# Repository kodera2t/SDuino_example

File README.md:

# SDuino_example
Once I was excited to see Intel's announce that they will release "SD card sized (SD card shaped) computer", 
but it was not true. This time I made a real SD card sized full programmable (indeed, Arduino pro compatible) 
small computer board, which is released at
https://hackaday.io/project/6435-sd-card-sized-board-lets-say-sduino
On this repository, I would upload practical application of SDuino. First one is "weather forecast SDuino" wich I2C pressure sensor
Have fun!

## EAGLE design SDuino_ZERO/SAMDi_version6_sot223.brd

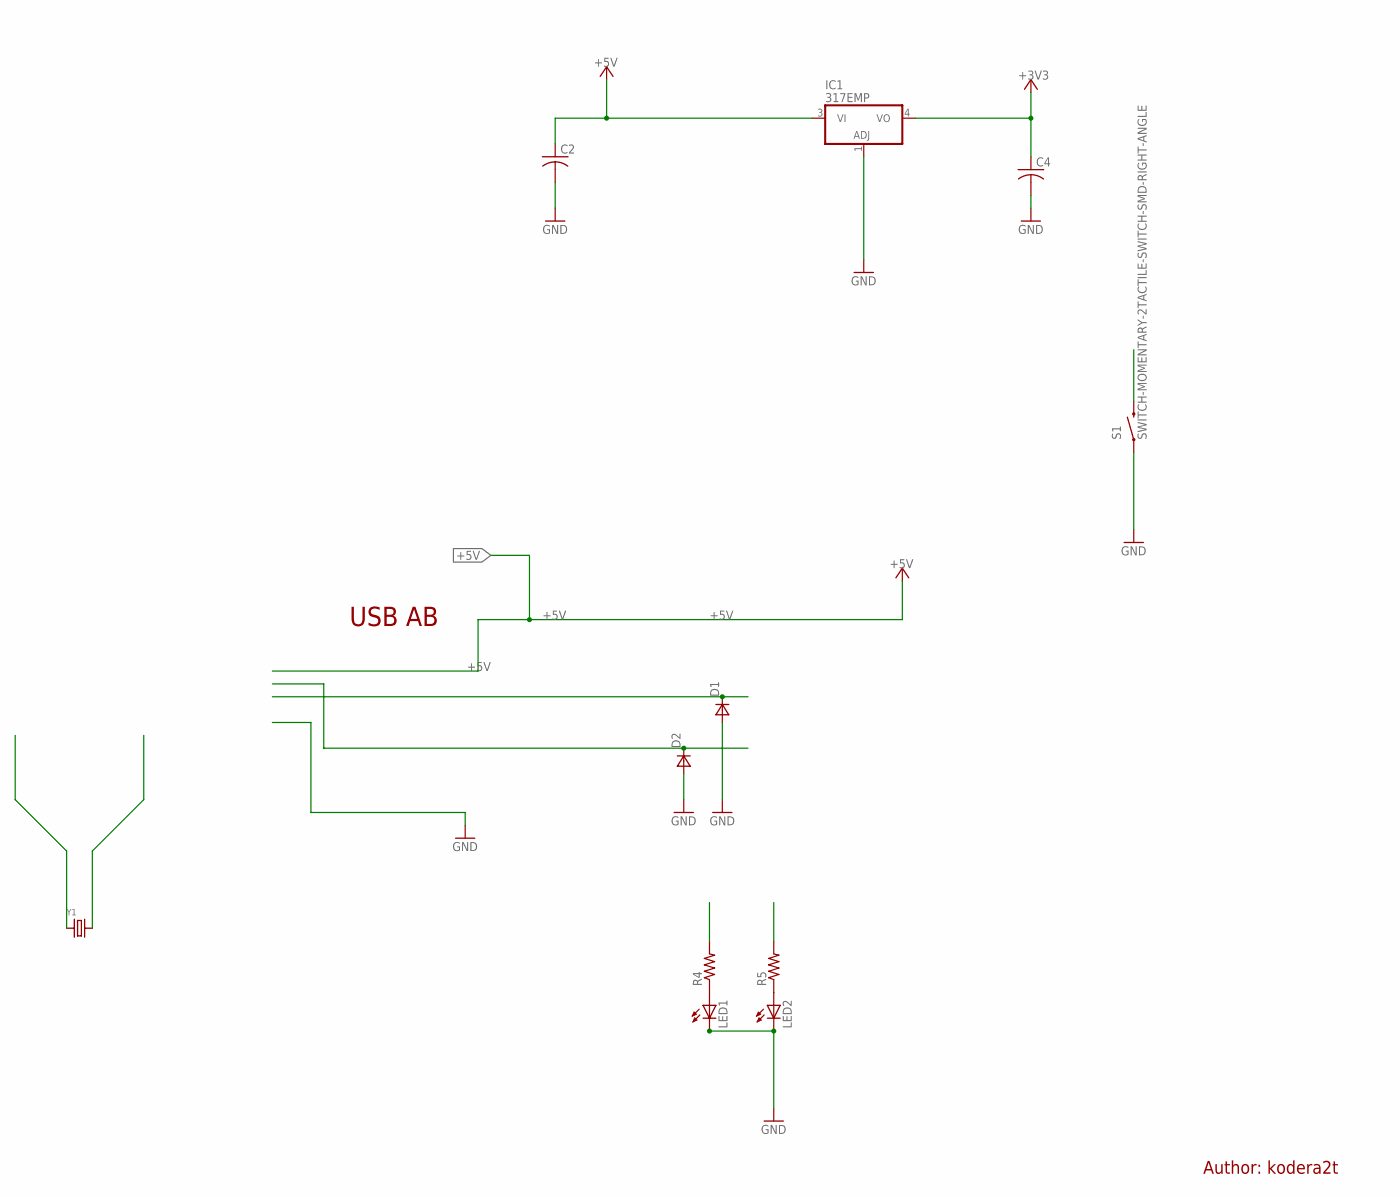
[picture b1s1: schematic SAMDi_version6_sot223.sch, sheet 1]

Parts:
C2, C4: C-USC0603; C0603
D1, D2: DSOD323; SOD323
IC1: 317EMP; SOT223
LED1, LED2: LEDCHIP-LED0603; CHIP-LED0603
R4, R5: R-US_R0603; R0603
S1: SWITCH-MOMENTARY-2TACTILE-SWITCH-SMD-RIGHT-ANGLE; TACTILE_SWITCH-SMD-RIGHT-ANGLE
Y1: CRYSTALTHIN32K; CRYSTAL_4.9X1.8

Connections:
+3V3: C4.1, IC1.4 (VO); also elsewhere on the board
+5V: C2.1, IC1.3 (VI)
GND: C2.2, C4.2, D1.2 (A), D2.2 (A), IC1.1 (ADJ), LED1.C, LED2.C, S1.1; also elsewhere on the board
LED1: R4.2; also elsewhere on the board
LED2: R5.2; also elsewhere on the board
unnamed: LED1.A, R4.1
unnamed: LED2.A, R5.1
TARGET_RESET: S1.2; also elsewhere on the board
TARGET_USB_N: D2.1 (C); also elsewhere on the board
TARGET_USB_P: D1.1 (C); also elsewhere on the board
XTAL11: Y1.2; also elsewhere on the board
XTAL22: Y1.1; also elsewhere on the board

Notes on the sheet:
USB AB
Author: kodera2t

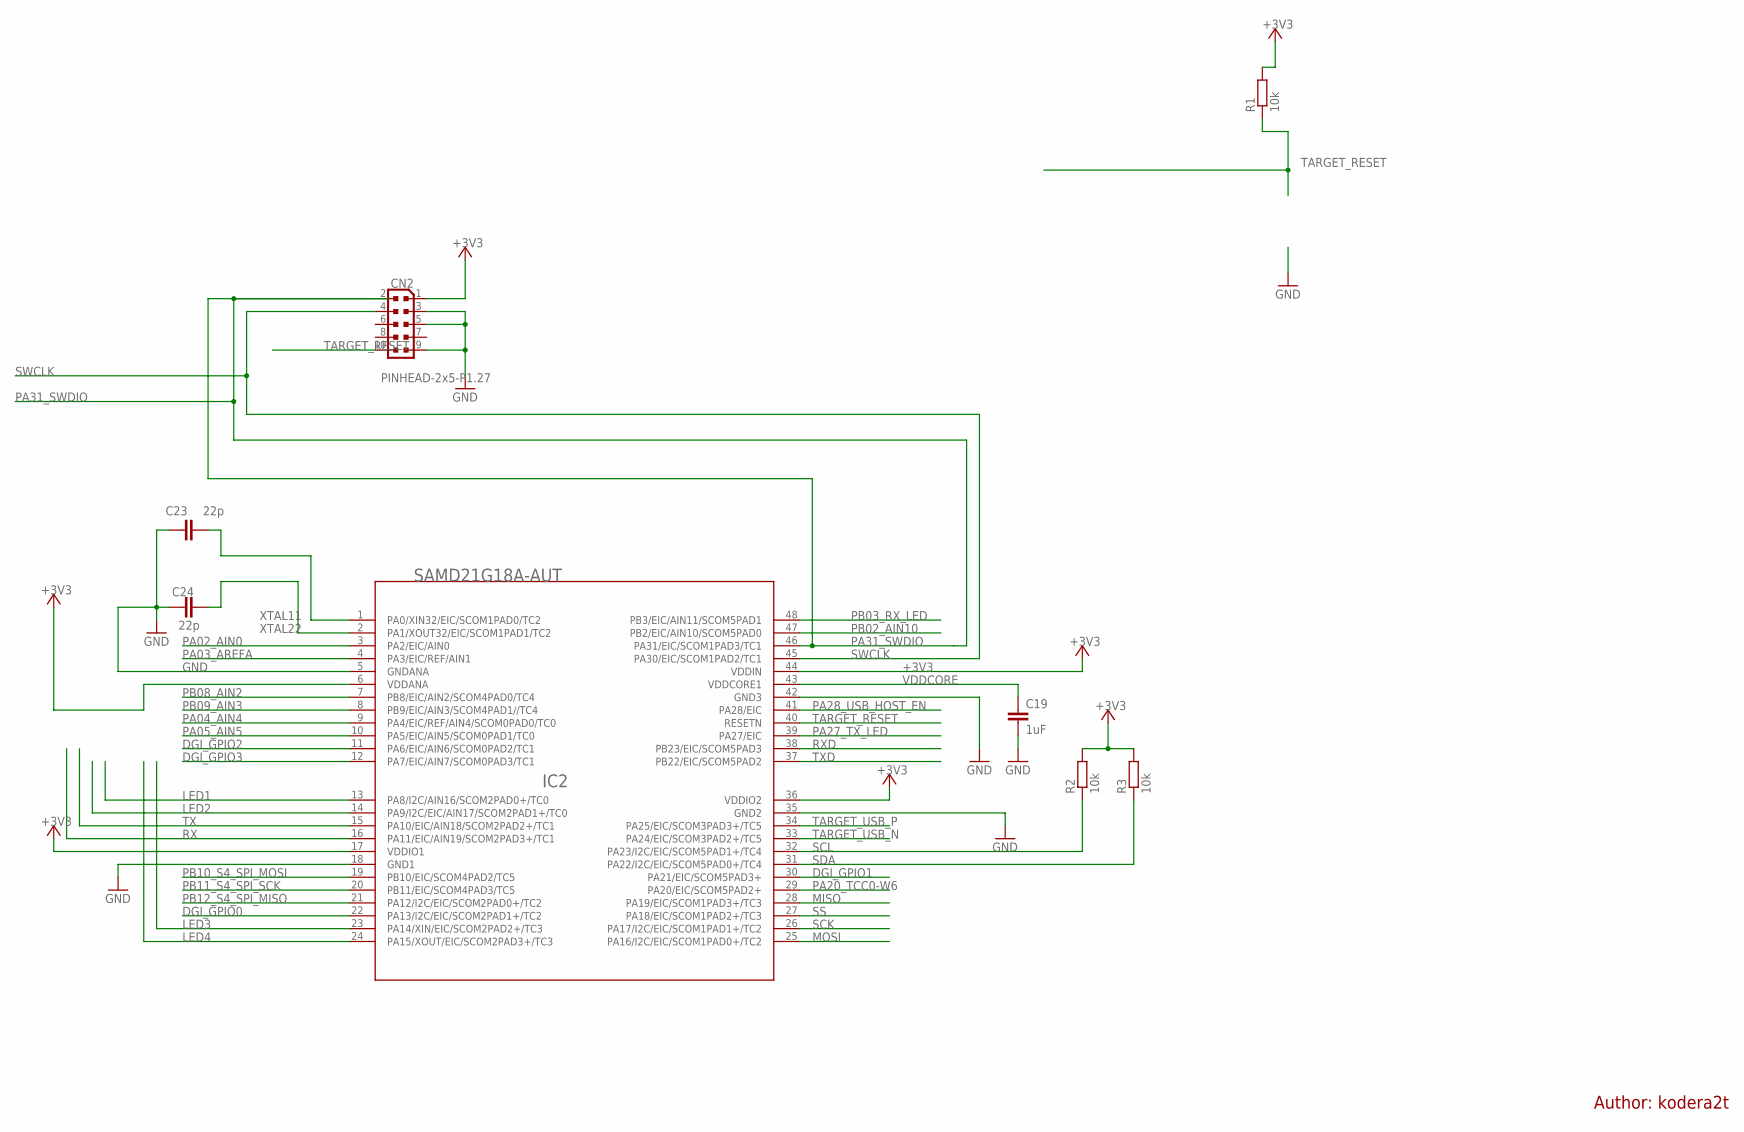
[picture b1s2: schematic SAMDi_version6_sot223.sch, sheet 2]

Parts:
C19: 1uF; C0603-ROUND
C23, C24: 22p; C0603-ROUND
CN2: PINHEAD-2x5-P1.27; PINHEAD_2X05_127
IC2: SAMD21G18A-AUT; TQFP48-7X7
R1, R2, R3: 10k; R0603-ROUND

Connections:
+3V3: CN2.1, IC2.6 (VDDANA), IC2.17 (VDDIO1), IC2.36 (VDDIO2), IC2.44 (VDDIN), R1.2, R2.2, R3.2; also elsewhere on the board
DGI_GPIO0: IC2.22 (PA13/I2C/EIC/SCOM2PAD1+/TC2)
DGI_GPIO1: IC2.30 (PA21/EIC/SCOM5PAD3+)
DGI_GPIO2: IC2.11 (PA6/EIC/AIN6/SCOM0PAD2/TC1)
DGI_GPIO3: IC2.12 (PA7/EIC/AIN7/SCOM0PAD3/TC1)
GND: C19.2, C23.1, C24.1, CN2.3, CN2.5, CN2.9, IC2.5 (GNDANA), IC2.18 (GND1), IC2.35 (GND2), IC2.42 (GND3); also elsewhere on the board
LED1: IC2.13 (PA8/I2C/AIN16/SCOM2PAD0+/TC0); also elsewhere on the board
LED2: IC2.14 (PA9/I2C/EIC/AIN17/SCOM2PAD1+/TC0); also elsewhere on the board
LED3: IC2.23 (PA14/XIN/EIC/SCOM2PAD2+/TC3)
LED4: IC2.24 (PA15/XOUT/EIC/SCOM2PAD3+/TC3)
MISO: IC2.28 (PA19/EIC/SCOM1PAD3+/TC3)
MOSI: IC2.25 (PA16/I2C/EIC/SCOM1PAD0+/TC2)
PA02_AIN0: IC2.3 (PA2/EIC/AIN0)
PA03_AREFA: IC2.4 (PA3/EIC/REF/AIN1)
PA04_AIN4: IC2.9 (PA4/EIC/REF/AIN4/SCOM0PAD0/TC0)
PA05_AIN5: IC2.10 (PA5/EIC/AIN5/SCOM0PAD1/TC0)
PA20_TCC0-W6: IC2.29 (PA20/EIC/SCOM5PAD2+)
PA27_TX_LED: IC2.39 (PA27/EIC)
PA28_USB_HOST_EN: IC2.41 (PA28/EIC)
PA31_SWDIO: CN2.2, IC2.46 (PA31/EIC/SCOM1PAD3/TC1)
PB02_AIN10: IC2.47 (PB2/EIC/AIN10/SCOM5PAD0)
PB03_RX_LED: IC2.48 (PB3/EIC/AIN11/SCOM5PAD1)
PB08_AIN2: IC2.7 (PB8/EIC/AIN2/SCOM4PAD0/TC4)
PB09_AIN3: IC2.8 (PB9/EIC/AIN3/SCOM4PAD1//TC4)
PB10_S4_SPI_MOSI: IC2.19 (PB10/EIC/SCOM4PAD2/TC5)
PB11_S4_SPI_SCK: IC2.20 (PB11/EIC/SCOM4PAD3/TC5)
PB12_S4_SPI_MISO: IC2.21 (PA12/I2C/EIC/SCOM2PAD0+/TC2)
RX: IC2.16 (PA11/EIC/AIN19/SCOM2PAD3+/TC1)
RXD: IC2.38 (PB23/EIC/SCOM5PAD3)
SCK: IC2.26 (PA17/I2C/EIC/SCOM1PAD1+/TC2)
SCL: IC2.32 (PA23/I2C/EIC/SCOM5PAD1+/TC4), R2.1
SDA: IC2.31 (PA22/I2C/EIC/SCOM5PAD0+/TC4), R3.1
SS: IC2.27 (PA18/EIC/SCOM1PAD2+/TC3)
SWCLK: CN2.4, IC2.45 (PA30/EIC/SCOM1PAD2/TC1)
TARGET_RESET: CN2.10, IC2.40 (RESETN), R1.1; also elsewhere on the board
TARGET_USB_N: IC2.33 (PA24/EIC/SCOM3PAD2+/TC5); also elsewhere on the board
TARGET_USB_P: IC2.34 (PA25/EIC/SCOM3PAD3+/TC5); also elsewhere on the board
TX: IC2.15 (PA10/EIC/AIN18/SCOM2PAD2+/TC1)
TXD: IC2.37 (PB22/EIC/SCOM5PAD2)
VDDCORE: C19.1, IC2.43 (VDDCORE1)
XTAL11: C23.2, IC2.1 (PA0/XIN32/EIC/SCOM1PAD0/TC2); also elsewhere on the board
XTAL22: C24.2, IC2.2 (PA1/XOUT32/EIC/SCOM1PAD1/TC2); also elsewhere on the board

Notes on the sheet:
Author: kodera2t

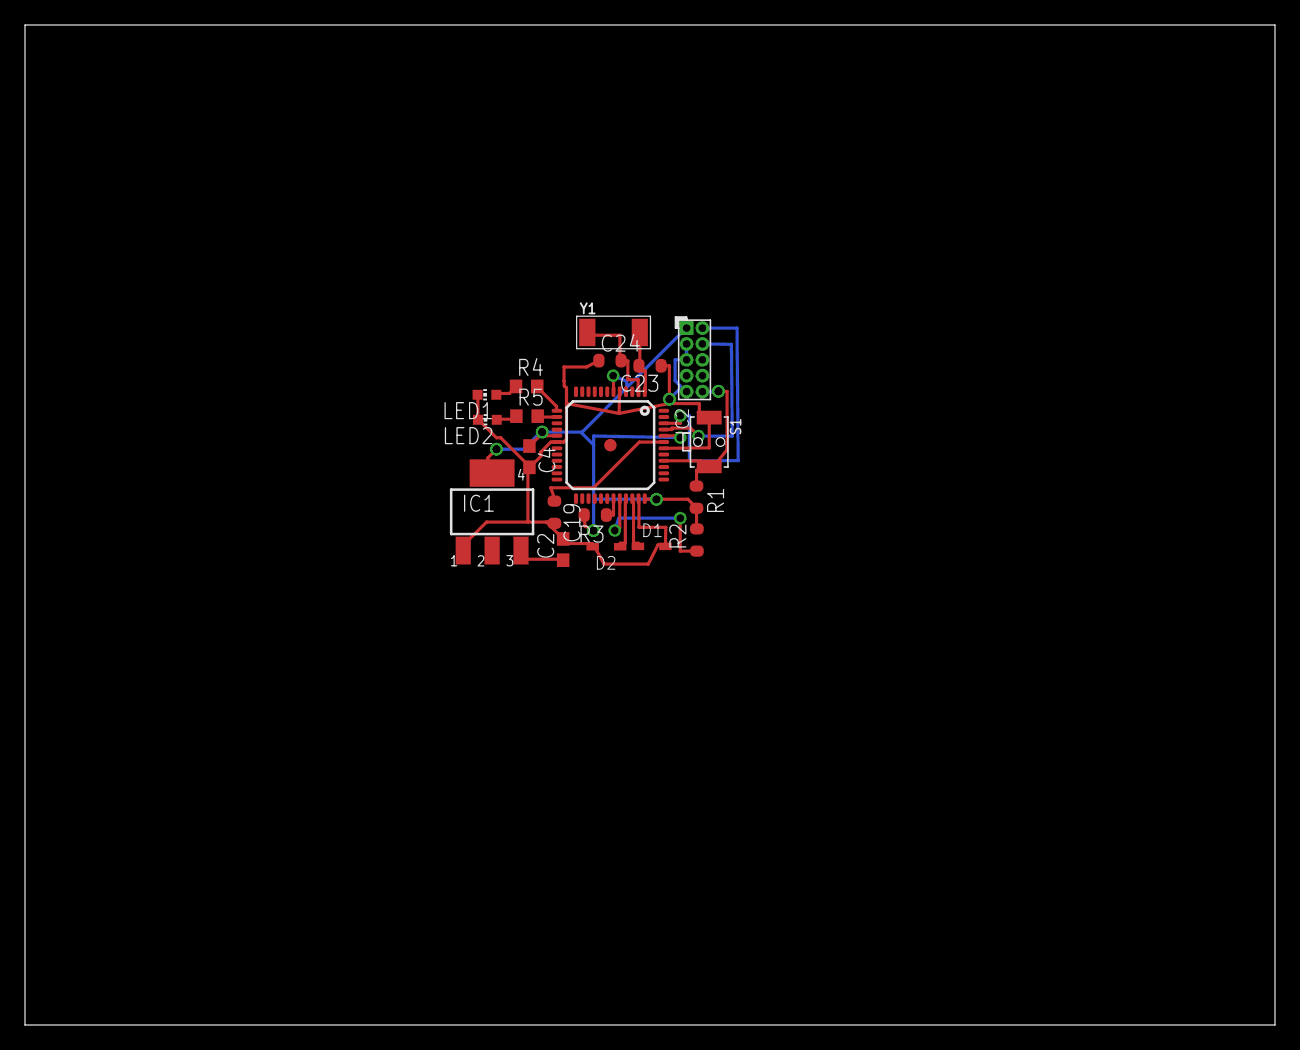
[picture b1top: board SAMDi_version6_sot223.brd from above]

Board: 2 copper layers, 100.0 x 80.0 mm, 19 parts (0 on the bottom side), 17 nets.

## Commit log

2015-07-09 SDuino first practical example
    SDuino first practical example, weather forecast by atmosphere pressure
    measurement
2015-08-30 SDuino Zero schematic

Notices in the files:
parts and their libraries:
microbuilder: This work is placed in the public domain, and may be freely used for commercial and non-commercial work with the following conditions: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
SparkFun-Electromechanical: Licensing: Creative Commons ShareAlike 4.0 International - https://creativecommons.org/licenses/by-sa/4.0
